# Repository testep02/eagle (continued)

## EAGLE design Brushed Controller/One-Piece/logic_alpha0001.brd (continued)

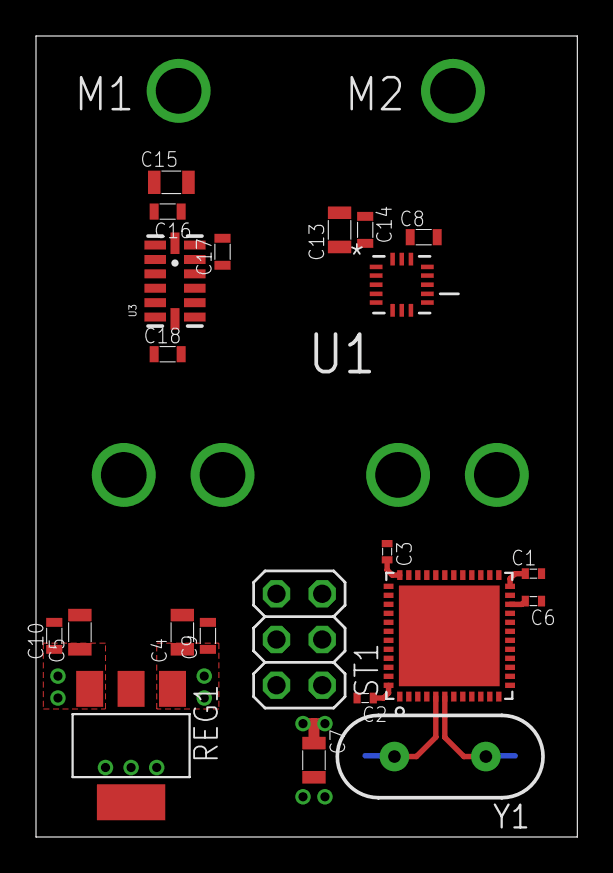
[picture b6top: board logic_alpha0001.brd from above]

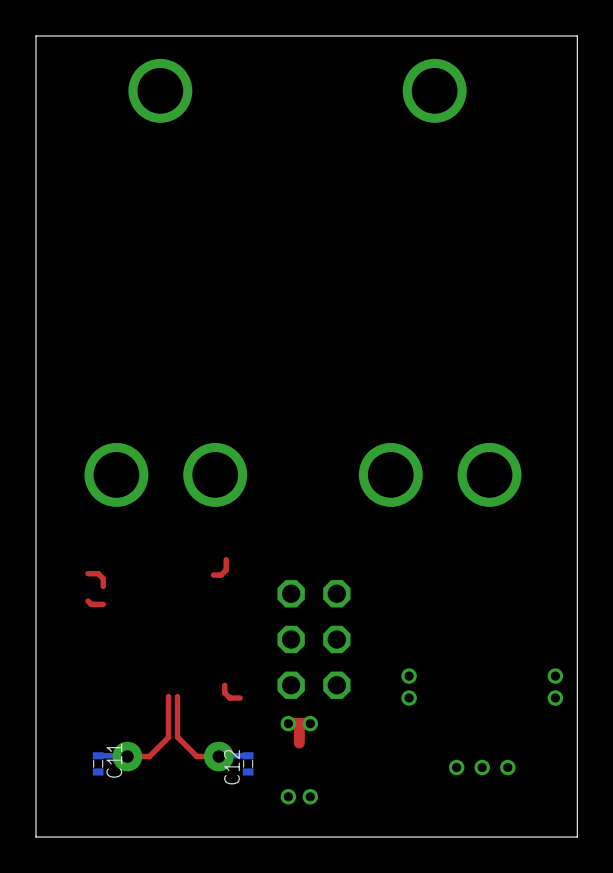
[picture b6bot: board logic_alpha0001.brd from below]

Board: 2 copper layers, 30.1 x 44.5 mm, 24 parts (2 on the bottom side), 15 nets.
